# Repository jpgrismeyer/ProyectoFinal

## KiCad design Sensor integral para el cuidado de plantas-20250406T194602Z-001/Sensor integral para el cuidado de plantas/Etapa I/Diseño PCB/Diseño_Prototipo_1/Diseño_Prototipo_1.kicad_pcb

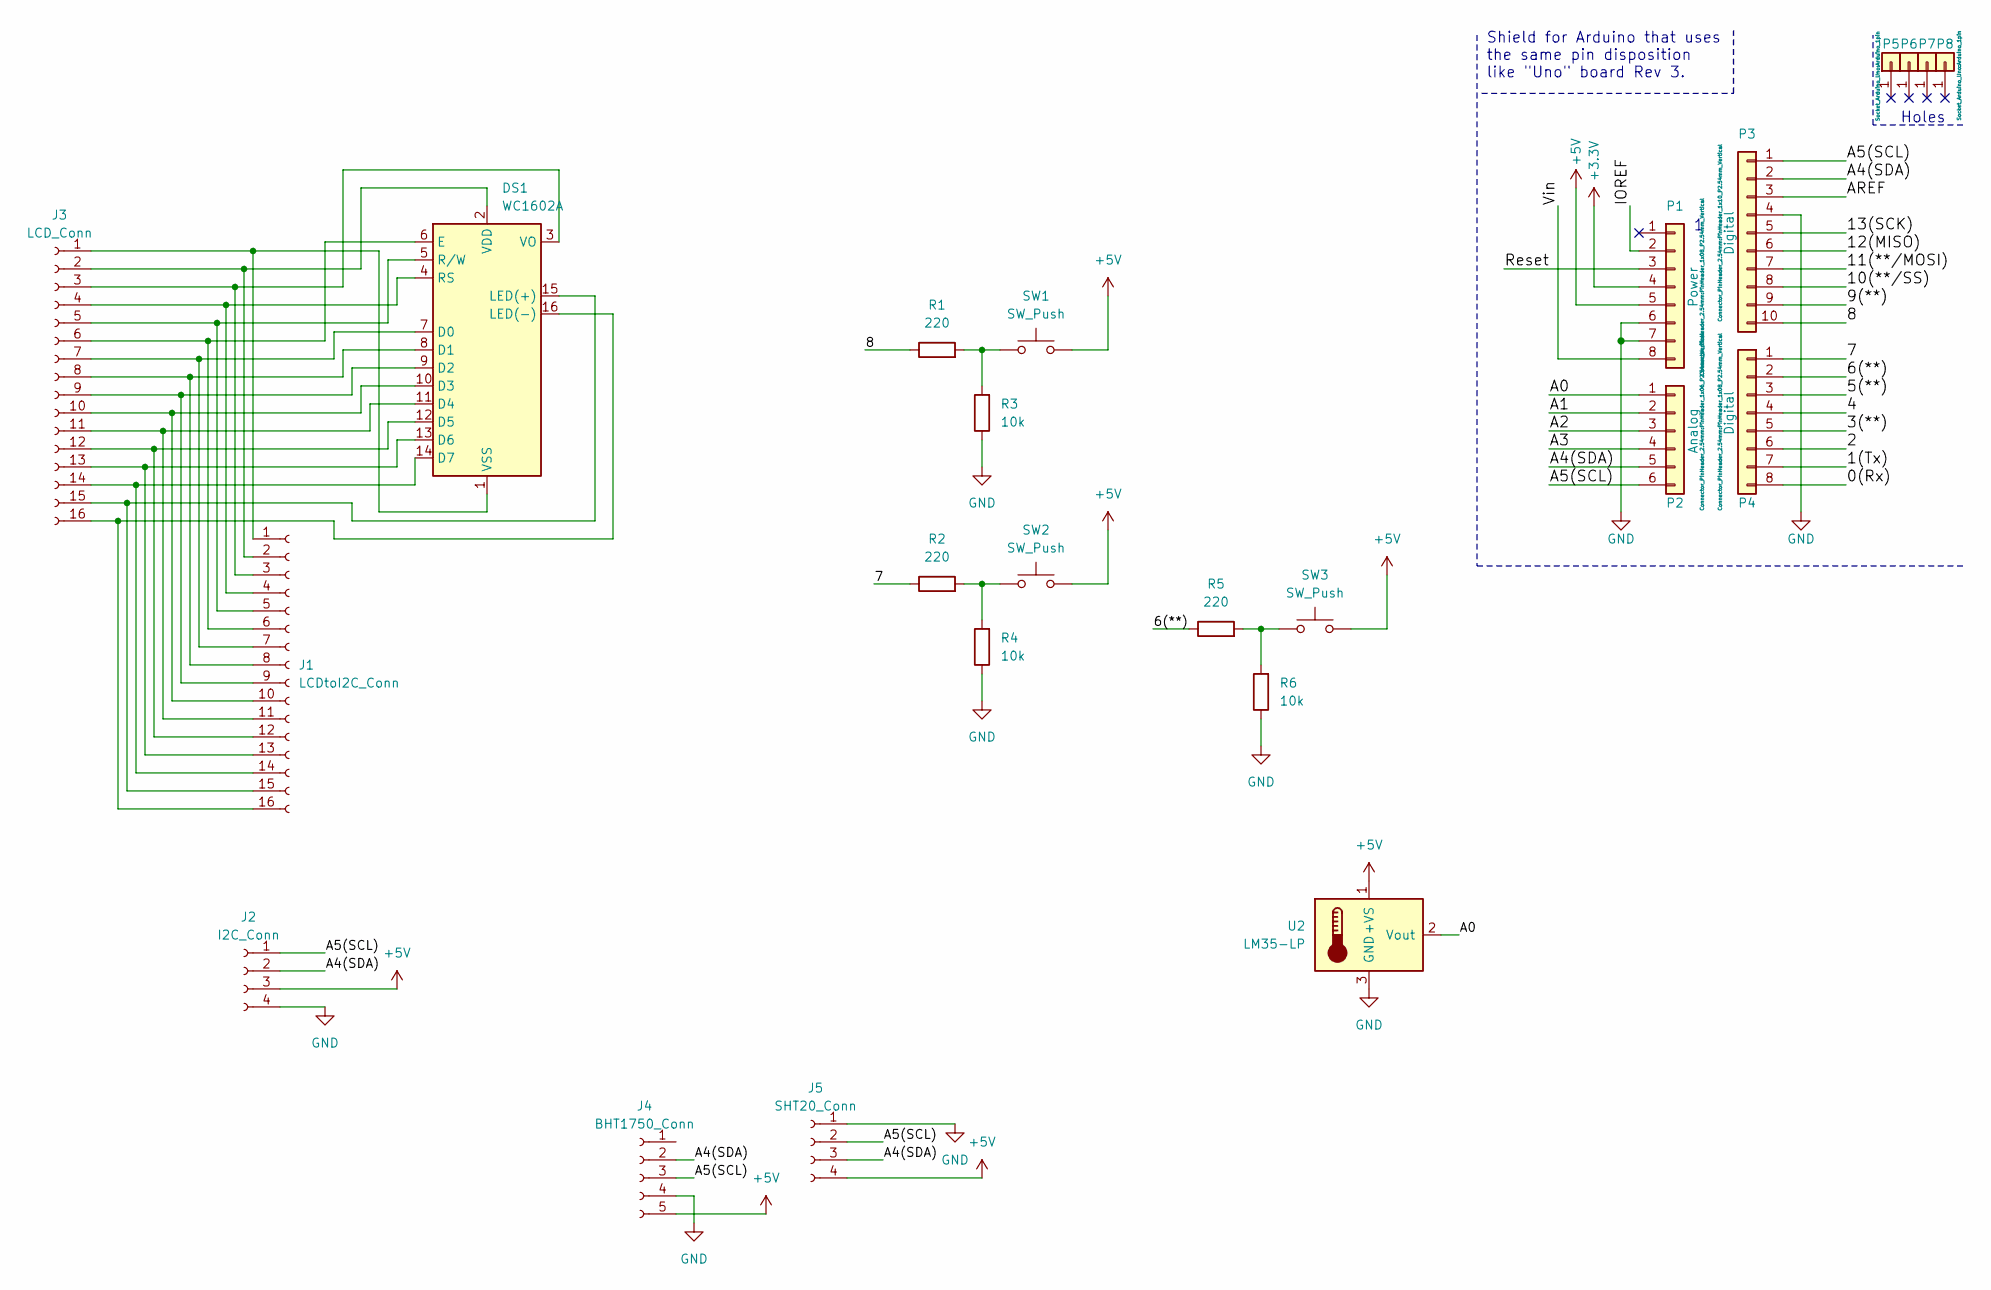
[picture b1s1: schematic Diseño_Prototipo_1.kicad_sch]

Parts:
DS1: WC1602A
J1: LCDtoI2C_Conn; PinSocket_1x16_P2.54mm_Vertical
J2: I2C_Conn; PinSocket_1x04_P2.54mm_Vertical
J3: LCD_Conn; PinSocket_1x16_P2.54mm_Vertical
J4: BHT1750_Conn; PinSocket_1x05_P2.54mm_Horizontal
J5: SHT20_Conn; PinSocket_1x04_P2.54mm_Vertical
P1: Power; PinHeader_1x08_P2.54mm_Vertical
P2: Analog; PinHeader_1x06_P2.54mm_Vertical
P3: Digital; PinHeader_1x10_P2.54mm_Vertical
P4: Digital; PinHeader_1x08_P2.54mm_Vertical
P5, P6, P7, P8: CONN_01X01; Arduino_1pin
R1, R2, R5: 220; R_Axial_DIN0207_L6.3mm_D2.5mm_P10.16mm_Horizontal
R3, R4, R6: 10k; R_Axial_DIN0207_L6.3mm_D2.5mm_P10.16mm_Horizontal
SW1, SW2, SW3: SW_Push; SW_PUSH_6mm
U2: LM35-LP; TO-92_Inline_Horizontal1

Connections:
+3V3: P1.4
+5V: J2.3, J4.5, J5.4, P1.5, SW1.2, SW2.2, SW3.2, U2.1 (+VS)
/0(Rx): P4.8
/1(Tx): P4.7
/2: P4.6
/3(**): P4.5
/4: P4.4
/5(**): P4.3
/6(**): P4.2, R5.1
/7: P4.1, R2.1
/8: P3.10, R1.1
/9(**): P3.9
/10(**/SS): P3.8
/11(**/MOSI): P3.7
/12(MISO): P3.6
/13(SCK): P3.5
/A0: P2.1, U2.2 (Vout)
/A1: P2.2
/A2: P2.3
/A3: P2.4
/A4(SDA): J2.2, J4.2, J5.3, P2.5, P3.2
/A5(SCL): J2.1, J4.3, J5.2, P2.6, P3.1
/AREF: P3.3
/IOREF: P1.2
/Reset: P1.3
/Vin: P1.8
GND: J2.4, J4.4, J5.1, P1.6, P1.7, P3.4, R3.1, R4.1, R6.1, U2.3 (GND)
unnamed: DS1.1 (VSS), J1.1, J3.1
unnamed: DS1.2 (VDD), J1.2, J3.2
unnamed: DS1.3 (VO), J1.3, J3.3
unnamed: DS1.4 (RS), J1.4, J3.4
unnamed: DS1.5 (R/W), J1.5, J3.5
unnamed: DS1.6 (E), J1.6, J3.6
unnamed: DS1.7 (D0), J1.7, J3.7
unnamed: DS1.8 (D1), J1.8, J3.8
unnamed: DS1.9 (D2), J1.9, J3.9
unnamed: DS1.10 (D3), J1.10, J3.10
unnamed: DS1.11 (D4), J1.11, J3.11
unnamed: DS1.12 (D5), J1.12, J3.12
unnamed: DS1.13 (D6), J1.13, J3.13
unnamed: DS1.14 (D7), J1.14, J3.14
unnamed: DS1.15 (LED(+)), J1.15, J3.15
unnamed: DS1.16 (LED(-)), J1.16, J3.16
unnamed: R1.2, R3.2, SW1.1
unnamed: R2.2, R4.2, SW2.1
unnamed: R5.2, R6.2, SW3.1

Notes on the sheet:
Holes
Shield for Arduino that uses the same pin disposition like "Uno" board Rev 3.

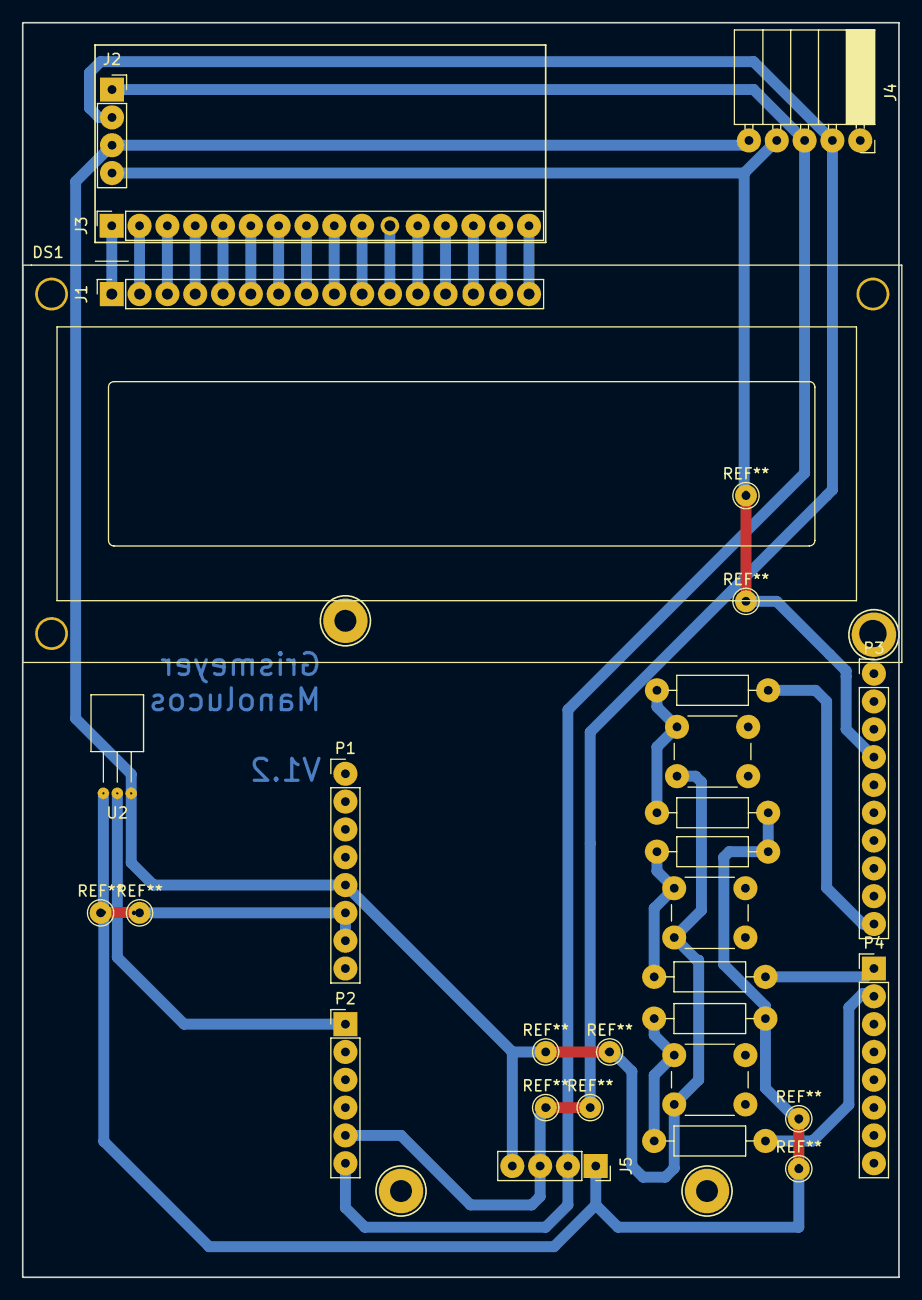
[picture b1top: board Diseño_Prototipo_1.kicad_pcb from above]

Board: 2 copper layers, 80.0 x 114.6 mm, 24 parts (0 on the bottom side), 27 nets.

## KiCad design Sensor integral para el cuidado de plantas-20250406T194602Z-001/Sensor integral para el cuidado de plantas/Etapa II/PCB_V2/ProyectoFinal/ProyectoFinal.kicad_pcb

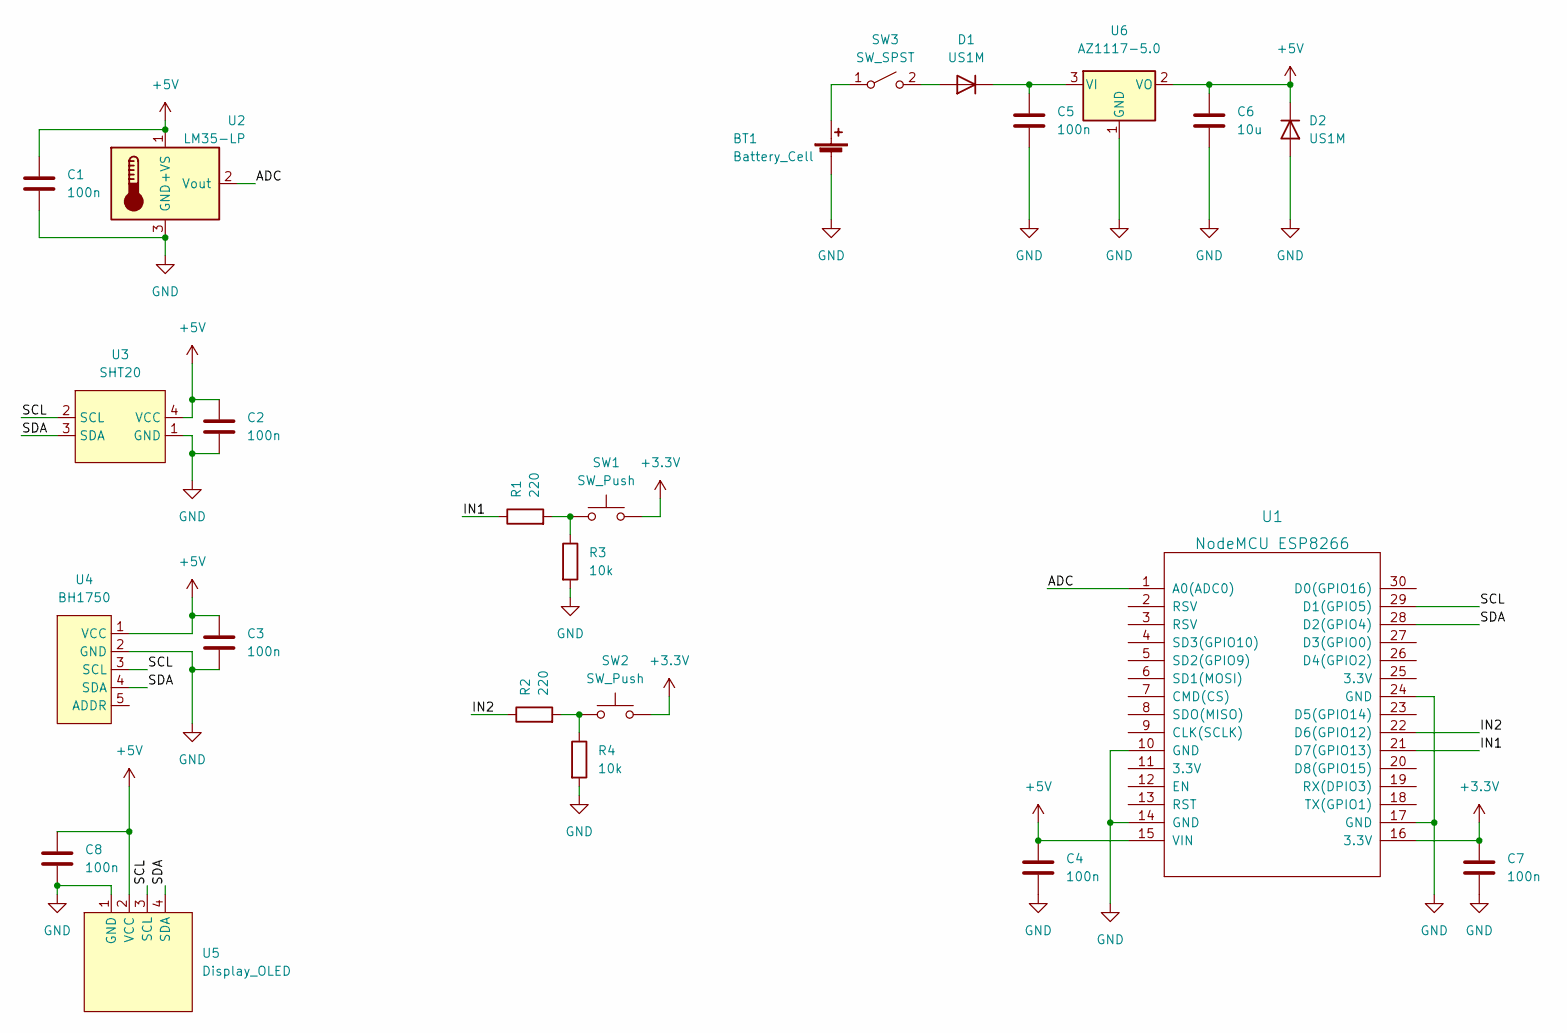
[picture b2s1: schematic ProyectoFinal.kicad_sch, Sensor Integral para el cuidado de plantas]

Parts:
BT1: Battery_Cell; Molex_KK-254_AE-6410-02A_1x02_P2.54mm_Vertical
C1, C2, C3, C4, C5, C7, C8: 100n; C_1206_3216Metric_Pad1.33x1.80mm_HandSolder
C6: 10u; CP_Radial_D5.0mm_P2.50mm
D1, D2: US1M; D_SMA
R1, R2: 220; R_1206_3216Metric_Pad1.30x1.75mm_HandSolder
R3, R4: 10k; R_1206_3216Metric_Pad1.30x1.75mm_HandSolder
SW1, SW2: SW_Push; SW_PUSH_6mm_H5mm
SW3: SW_SPST; SW_E-Switch_EG2219_DPDT_Angled
U1: NodeMCU ESP8266; ESP12F-Devkit-V3
U2: LM35-LP; TO-92_Inline_Wide
U3: SHT20; PinSocket_1x04_P2.54mm_Vertical
U4: BH1750; PinSocket_1x05_P2.54mm_Vertical
U5: Display_OLED; PinSocket_1x04_P2.54mm_Vertical
U6: AZ1117-5.0; SOT-223

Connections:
+3V3: C7.1, SW1.2, SW2.2, U1.16 (3.3V)
+5V: C1.1, C2.1, C3.1, C4.1, C6.1, C8.1, D2.1 (K), U1.15 (VIN), U2.1 (+VS), U3.4 (VCC), U4.1 (VCC), U5.2 (VCC), U6.2 (VO)
/ADC: U1.1 (A0(ADC0)), U2.2 (Vout)
/IN1: R1.1, U1.21 (D7(GPIO13))
/IN2: R2.1, U1.22 (D6(GPIO12))
/SCL: U1.29 (D1(GPIO5)), U3.2 (SCL), U4.3 (SCL), U5.3 (SCL)
/SDA: U1.28 (D2(GPIO4)), U3.3 (SDA), U4.4 (SDA), U5.4 (SDA)
GND: BT1.2 (-), C1.2, C2.2, C3.2, C4.2, C5.2, C6.2, C7.2, C8.2, D2.2 (A), R3.2, R4.2, U1.10 (GND), U1.14 (GND), U1.17 (GND), U1.24 (GND), U2.3 (GND), U3.1 (GND), U4.2 (GND), U5.1 (GND), U6.1 (GND)
unnamed: BT1.1 (+), SW3.1 (A)
unnamed: C5.1, D1.1 (K), U6.3 (VI)
unnamed: D1.2 (A), SW3.2 (B)
unnamed: R1.2, R3.1, SW1.1
unnamed: R2.2, R4.1, SW2.1

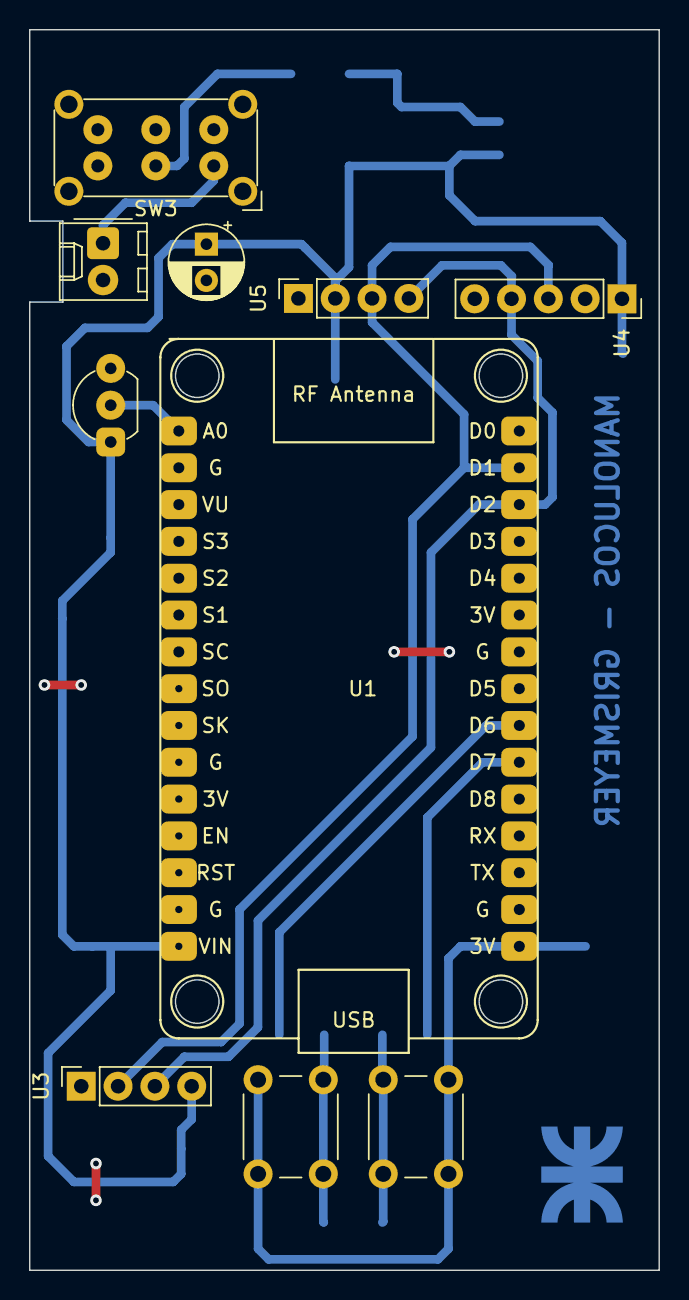
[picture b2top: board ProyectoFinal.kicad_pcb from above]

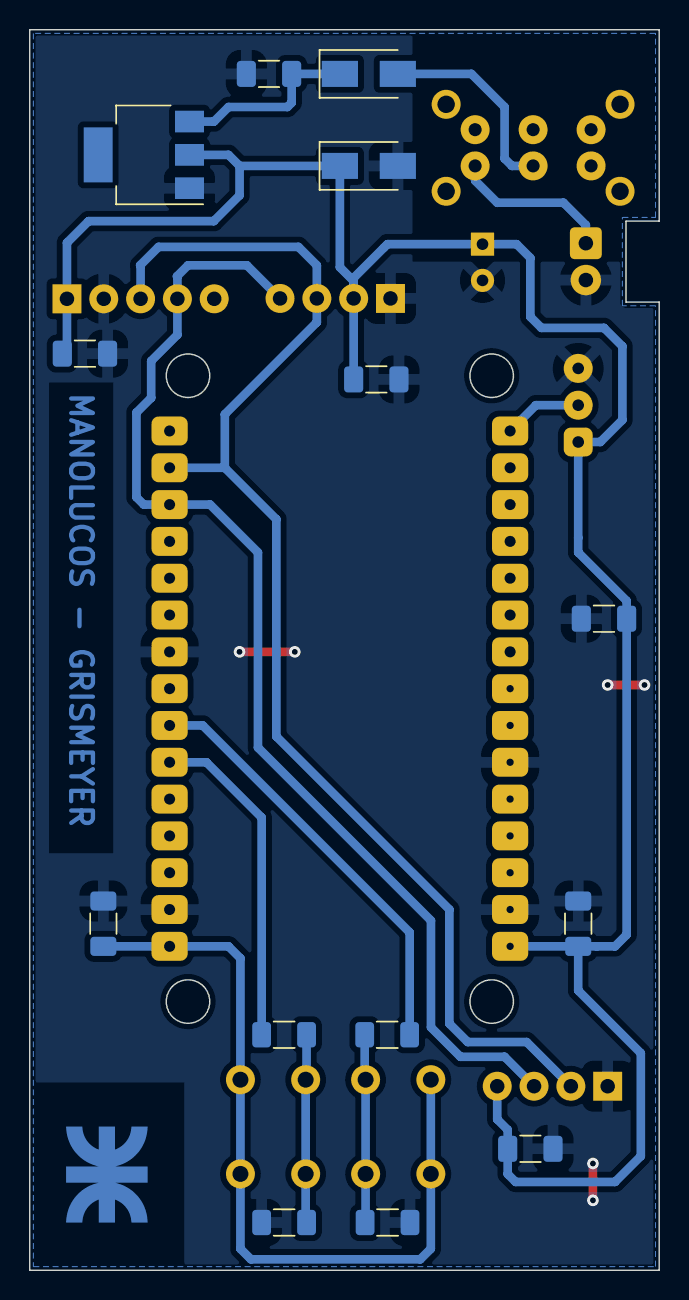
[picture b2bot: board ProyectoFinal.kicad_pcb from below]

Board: 2 copper layers, 43.4 x 85.6 mm, 24 parts (14 on the bottom side), 13 nets.

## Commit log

2025-04-06 Proyecto Final: Sensor integral para el cuidado de plantas
2025-04-06 Proyecto presentado el 8/7/22
